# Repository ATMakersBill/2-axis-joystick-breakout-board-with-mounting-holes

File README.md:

# Version of the Joystick breakout board that maps well into the XBox Adaptive Controller

Adafruit's board is great, but the XAC wants the switch to short to VCC, not GND,
and it's easier for us to put 3.5mm PTH components on this board than to wire it up.

Remaining Readme is from Adafruit.  Thank you, Adafruit for this great work.

# PCB files for breakout board for Analog 2-axis Thumb Joystick with Select Button

<a href="http://www.adafruit.com/products/512"><br/>
Click here to purchase one from the Adafruit shop
</a>

This mini-kit makes it easy to mount a PSP/Xbox-like thumb joystick to your project. The thumbstick is an analog joystick - more accurate and sensitive than just 'directional' joysticks - with a 'press in to select' button. Since it's analog, you'll need two analog reading pins on your microcontroller to determine X and Y. Having an extra digital input will let you read the switch.

The pack comes in three parts - the joystick itself, a soft-touch rubber 'hat' and a nicely designed breakout board. We designed the breakout so that you can attach the joystick to a panel easily - every other breakout we wanted to carry had the mounting holes so they were in the way of the joystick movement! A 5 pin 0.1" spaced header makes it easy to connect either in a perfboard/breadboard setting or free wiring. You'll need to solder the joystick into the PCB using a soldering iron and solder, but its very simple and will only take a minute.

## License

Adafruit invests time and resources providing this open source design, 
please support Adafruit and open-source hardware by purchasing 
products from Adafruit!

Designed by Adafruit Industries.  
Creative Commons Attribution, Share-Alike license, check license.txt for more information
All text above must be included in any redistribution

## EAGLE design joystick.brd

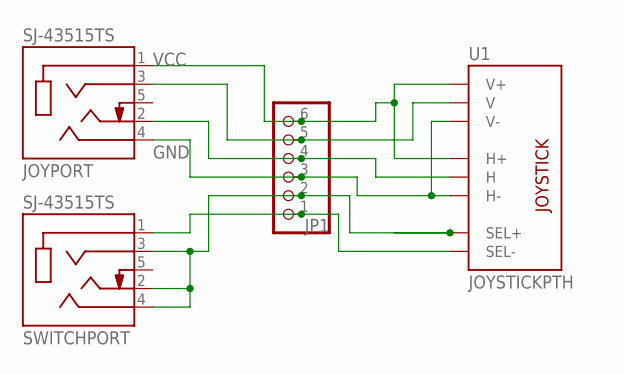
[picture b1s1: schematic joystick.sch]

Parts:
JOYPORT: SJ-43515TS; CUI_SJ-43515TS
JP1: PINHD-1X6B; 1X06-BIG
SWITCHPORT: SJ-43515TS; CUI_SJ-43515TS
U1: JOYSTICKPTH; JOYSTICK

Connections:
GND: JOYPORT.4 (RING2), JP1.3, U1.H3 (H-), U1.V3 (V-)
unnamed: JP1.2, SWITCHPORT.2 (TIP), SWITCHPORT.3 (RING1), SWITCHPORT.4 (RING2), U1.B1A (SEL+)
unnamed: JOYPORT.3 (RING1), JP1.5, U1.V2 (V)
unnamed: JOYPORT.2 (TIP), JP1.4, U1.H2 (H)
unnamed: JP1.1, SWITCHPORT.1 (SLEEVE), U1.B2A (SEL-)
VCC: JOYPORT.1 (SLEEVE), JP1.6, U1.H1 (H+), U1.V1 (V+)

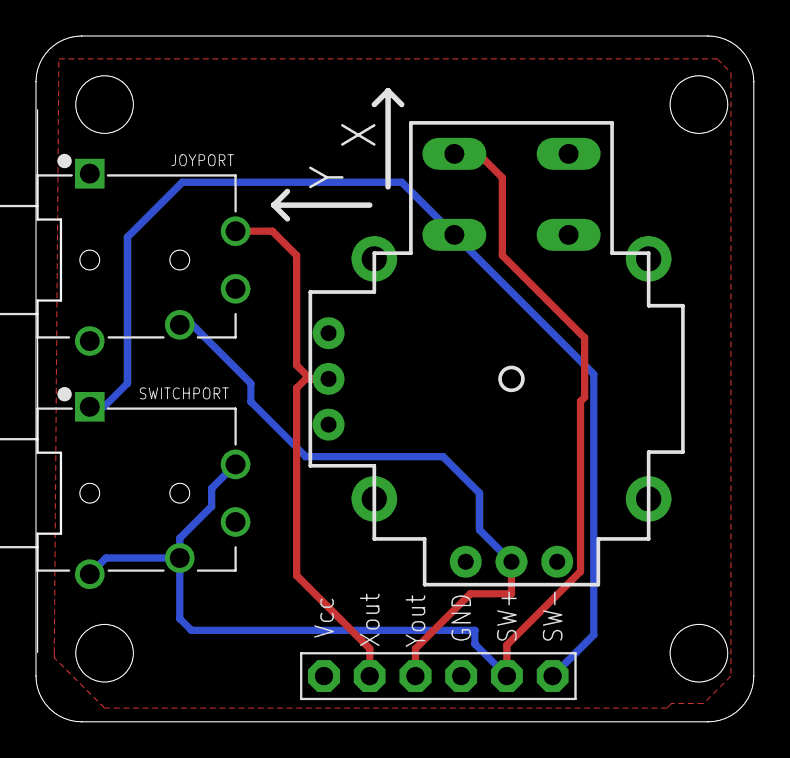
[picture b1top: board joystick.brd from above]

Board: 2 copper layers, 39.9 x 38.1 mm, 4 parts (0 on the bottom side), 6 nets.

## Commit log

2020-02-09 Initial upload of fork
2020-02-09 Adding pix for readme
2020-02-09 Readme Changes
2020-02-09 Adding Pictures
2020-02-16 Adding Pix and tweaks to board
